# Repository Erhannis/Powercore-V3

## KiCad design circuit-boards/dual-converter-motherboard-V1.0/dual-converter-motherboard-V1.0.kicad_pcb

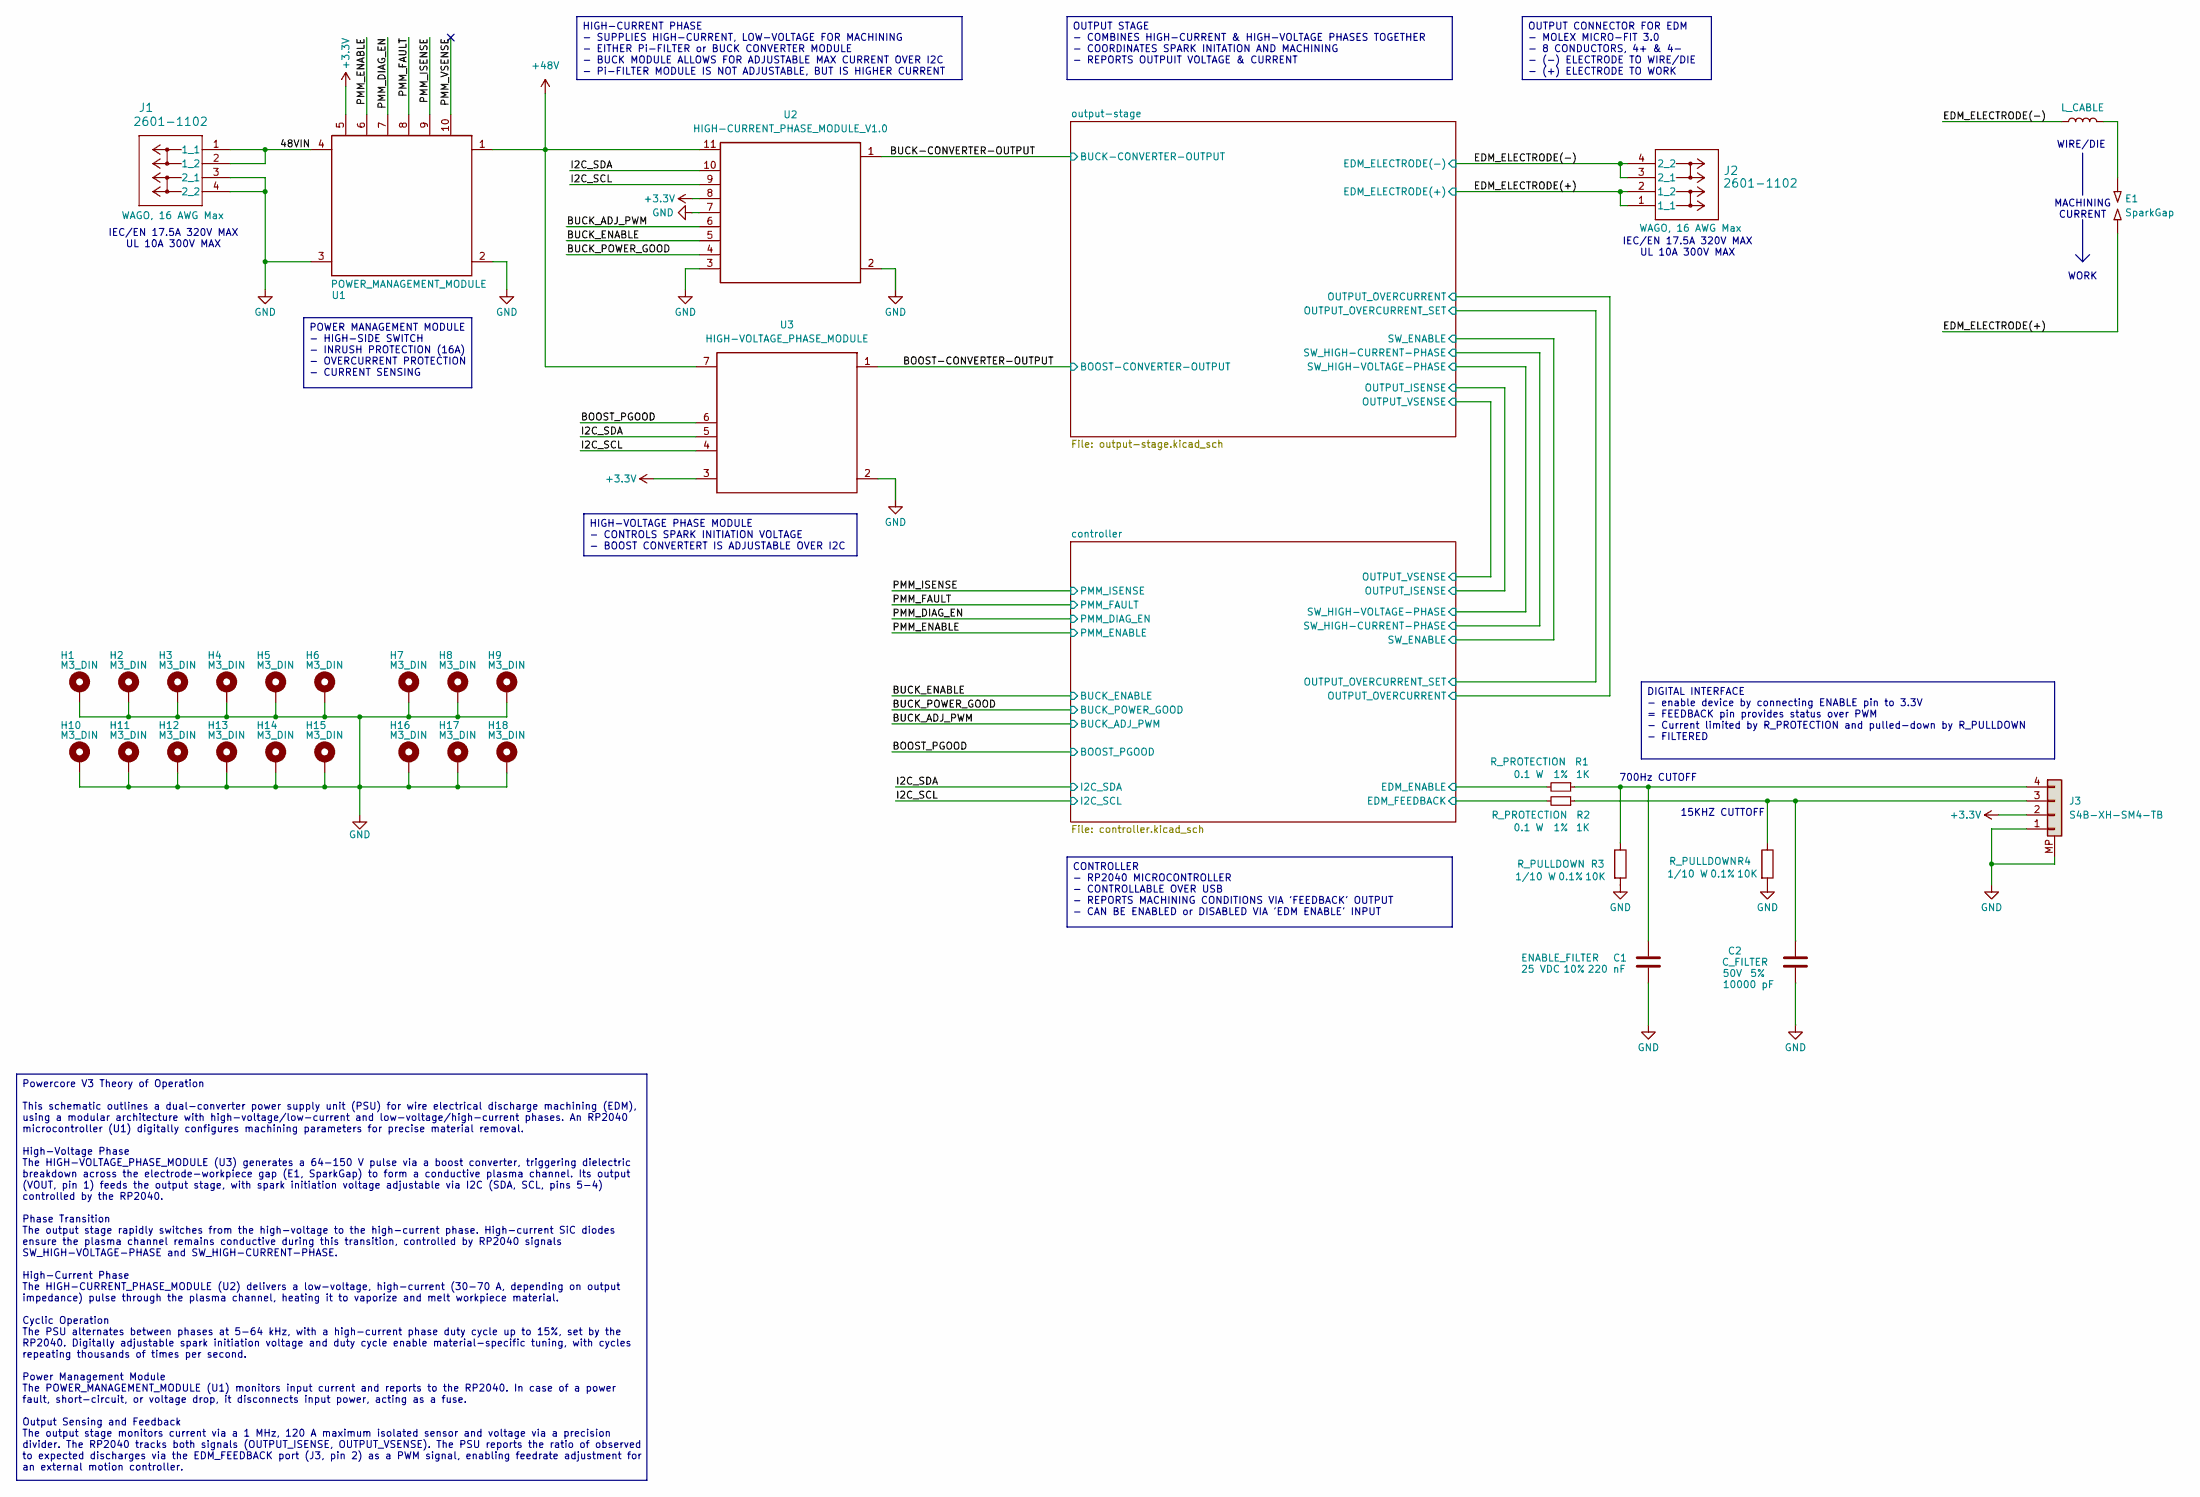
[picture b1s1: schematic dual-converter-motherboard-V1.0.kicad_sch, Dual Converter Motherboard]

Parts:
C1: 220 nF; C_0603_1608Metric; Tolerance 10%; Max Voltage 25 VDC; Manufacturer# AC0603KRX7R9BB224; LCSC Part # C726565
C2: 10000 pF; C_0603_1608Metric; Tolerance 5%; Max Voltage 50V; Manufacturer# CC0603JRX7R9BB103; LCSC Part # C115056
E1: SparkGap; NULL; Manufacturer# NULL; LCSC Part # NULL
H1, H2, H3, H4, H5, H6, H7, H8, H9, H10, H11, H12, H13, H14, H15, H16, H17, H18: M3_DIN; MountingHole_3.2mm_M3_DIN965_Pad_TopBottom; Manufacturer# NULL
J1, J2: 2601-1102; Manufacturer# 2601-1102; LCSC Part # C7509568
J3: S4B-XH-SM4-TB; Manufacturer# S4B-XH-SM4-TB; LCSC Part # C161861
L_CABLE1: L_CABLE
R1, R2: 1K; R_0603_1608Metric; Tolerance 1%; Manufacturer# RC0603FR-071KL; LCSC Part # C22548
R3, R4: 10K; R_0603_1608Metric; Tolerance 0.1%; Manufacturer# RC0603BR-0710KL; LCSC Part # C95204
U1: POWER_MANAGEMENT_MODULE; POWER_MANAGEMENT_MODULE_FOOTPRINT_V1.0
U2: HIGH-CURRENT_PHASE_MODULE_V1.0; HIGH-CURRENT_PHASE_MODULE_FOOTPRINT_V1.0
U3: HIGH-VOLTAGE_PHASE_MODULE; HIGH-VOLTAGE_PHASE_MODULE_FOOTPRINT_V1.0

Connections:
+3.3V: J3.2, U1.5, U2.8 (3.3VIN), U3.3 (GND); also elsewhere on the board
+48V: U1.1 (VOUT), U2.11 (48VIN), U3.7 (48VIN); also elsewhere on the board
/48VIN: J1.1 (1_1), J1.2 (1_2), U1.4 (VIN)
/BOOST-CONVERTER-OUTPUT: U3.1 (VOUT); also elsewhere on the board
/BOOST_PGOOD: U3.6 (PGOOD); also elsewhere on the board
/BUCK-CONVERTER-OUTPUT: U2.1 (VOUT); also elsewhere on the board
/BUCK_ADJ_PWM: U2.6 (PWM_ADJ); also elsewhere on the board
/BUCK_ENABLE: U2.5 (ENABLE); also elsewhere on the board
/BUCK_POWER_GOOD: U2.4 (PGOOD); also elsewhere on the board
/EDM_ELECTRODE(+): E1.1, J2.1 (1_1), J2.2 (1_2); also elsewhere on the board
/EDM_ELECTRODE(-): J2.3 (2_1), J2.4 (2_2), L_CABLE1.1; also elsewhere on the board
/I2C_SCL: U2.9 (SCL), U3.4 (SCL); also elsewhere on the board
/I2C_SDA: U2.10 (SDA), U3.5 (SDA); also elsewhere on the board
/PMM_DIAG_EN: U1.7; also elsewhere on the board
/PMM_ENABLE: U1.6; also elsewhere on the board
/PMM_FAULT: U1.8; also elsewhere on the board
/PMM_ISENSE: U1.9; also elsewhere on the board
/PMM_VSENSE: U1.10
/PMM_VSENSE_1: U1.10
/controller/EDM_ENABLE: R1.2; also elsewhere on the board
/controller/EDM_FEEDBACK: R2.2; also elsewhere on the board
GND: C1.2, C2.2, H1.1, H2.1, H3.1, H4.1, H5.1, H6.1, H7.1, H8.1, H9.1, H10.1, H11.1, H12.1, H13.1, H14.1, H15.1, H16.1, H17.1, H18.1, J1.3 (2_1), J1.4 (2_2), J3.1, J3.MP, R3.2, R4.2, U1.2, U1.3, U2.2 (GND), U2.3 (GND), U2.7 (GND), U3.2 (GND); also elsewhere on the board
unnamed: E1.2, L_CABLE1.2
unnamed: C2.1, J3.3, R2.1, R4.1
unnamed: C1.1, J3.4, R1.1, R3.1

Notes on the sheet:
IEC/EN 17.5A 320V MAX UL 10A 300V MAX
WORK
700Hz CUTOFF
MACHINING CURRENT
WIRE/DIE
15KHZ CUTTOFF
CONTROLLER - RP2040 MICROCONTROLLER - CONTROLLABLE OVER USB - REPORTS MACHINING CONDITIONS VIA 'FEEDBACK' OUTPUT - CAN BE ENABLED or DISABLED VIA 'EDM ENABLE' INPUT
HIGH-VOLTAGE PHASE MODULE - CONTROLS SPARK INITIATION VOLTAGE - BOOST CONVERTERT IS ADJUSTABLE OVER I2C
OUTPUT CONNECTOR FOR EDM - MOLEX MICRO-FIT 3.0 - 8 CONDUCTORS, 4+ & 4- - (-) ELECTRODE TO WIRE/DIE - (+) ELECTRODE TO WORK
HIGH-CURRENT PHASE - SUPPLIES HIGH-CURRENT, LOW-VOLTAGE FOR MACHINING - EITHER Pi-FILTER or BUCK CONVERTER MODULE - BUCK MODULE ALLOWS FOR ADJUSTABLE MAX CURRENT OVER I2C - Pi-FILTER MODULE IS NOT ADJUSTABLE, BUT IS HIGHER CURRENT
Powercore V3 Theory of Operation This schematic outlines a dual-converter power supply unit (PSU) for wire electrical discharge machining (EDM), using a modular architecture with high-voltage/low-current and low-voltage/high-current phases. An RP2040 microcontroller (U1) digitally configures machin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
OUTPUT STAGE - COMBINES HIGH-CURRENT & HIGH-VOLTAGE PHASES TOGETHER - COORDINATES SPARK INITATION AND MACHINING - REPORTS OUTPUIT VOLTAGE & CURRENT
POWER MANAGEMENT MODULE - HIGH-SIDE SWITCH - INRUSH PROTECTION (16A) - OVERCURRENT PROTECTION - CURRENT SENSING
DIGITAL INTERFACE - enable device by connecting ENABLE pin to 3.3V = FEEDBACK pin provides status over PWM - Current limited by R_PROTECTION and pulled-down by R_PULLDOWN - FILTERED

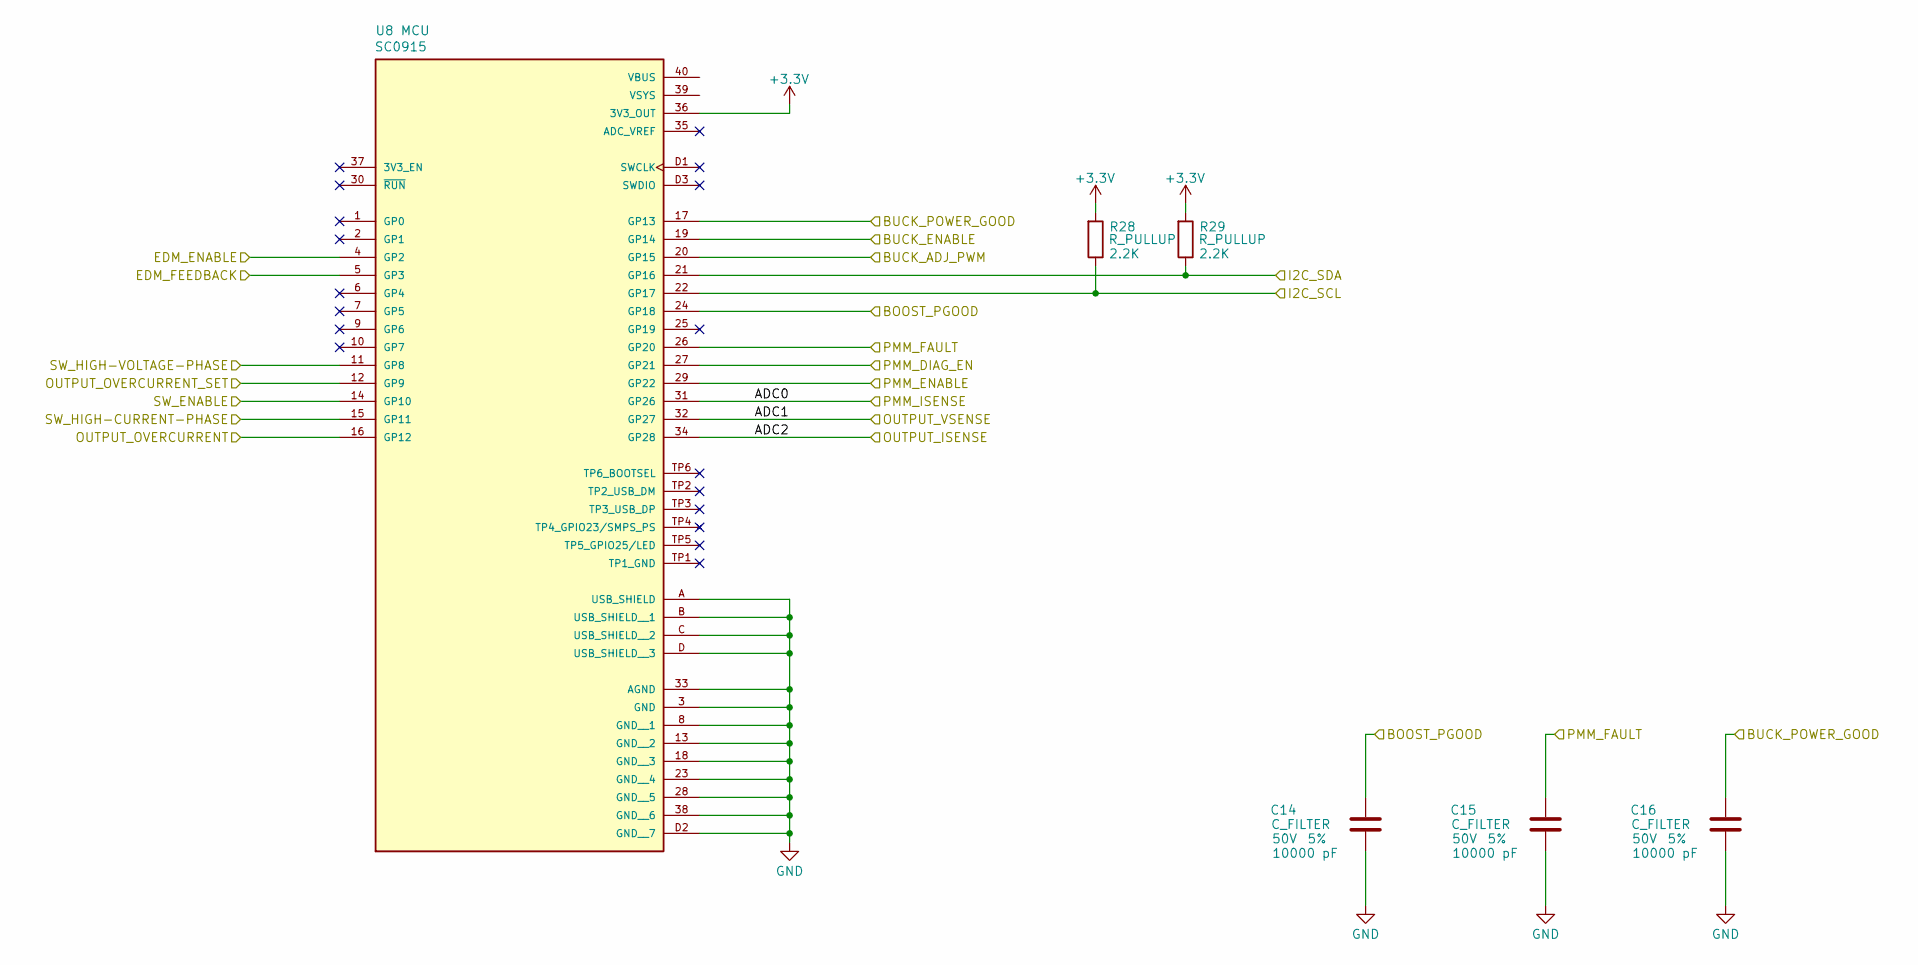
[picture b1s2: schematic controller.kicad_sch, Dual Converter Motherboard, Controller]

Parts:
C14, C15, C16: 10000 pF; C_0603_1608Metric; Tolerance 5%; Max Voltage 50V; Manufacturer# CC0603JRX7R9BB103; LCSC Part # C115056
R28, R29: 2.2K; R_0603_1608Metric; Tolerance 1%; Manufacturer# RC0603FR-132K2L; LCSC Part # C3032396
U8: SC0915; Manufacturer# SC0915; LCSC Part # C7203002

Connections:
+3.3V: R28.2, R29.2, U8.36 (3V3_OUT); also elsewhere on the board
/BOOST_PGOOD: C14.1, U8.24 (GP18); also elsewhere on the board
/BUCK_ADJ_PWM: U8.20 (GP15); also elsewhere on the board
/BUCK_ENABLE: U8.19 (GP14); also elsewhere on the board
/BUCK_POWER_GOOD: C16.1, U8.17 (GP13); also elsewhere on the board
/I2C_SCL: R28.1, U8.22 (GP17); also elsewhere on the board
/I2C_SDA: R29.1, U8.21 (GP16); also elsewhere on the board
/PMM_DIAG_EN: U8.27 (GP21); also elsewhere on the board
/PMM_ENABLE: U8.29 (GP22); also elsewhere on the board
/PMM_FAULT: C15.1, U8.26 (GP20); also elsewhere on the board
/PMM_ISENSE: U8.31 (GP26); also elsewhere on the board
/controller/ADC1: U8.32 (GP27); also elsewhere on the board
/controller/ADC2: U8.34 (GP28); also elsewhere on the board
/controller/EDM_ENABLE: U8.4 (GP2); also elsewhere on the board
/controller/EDM_FEEDBACK: U8.5 (GP3); also elsewhere on the board
/controller/OUTPUT_OVERCURRENT: U8.16 (GP12); also elsewhere on the board
/controller/OUTPUT_OVERCURRENT_SET: U8.12 (GP9); also elsewhere on the board
/controller/SW_ENABLE: U8.14 (GP10); also elsewhere on the board
/controller/SW_HIGH-CURRENT-PHASE: U8.15 (GP11); also elsewhere on the board
/controller/SW_HIGH-VOLTAGE-PHASE: U8.11 (GP8); also elsewhere on the board
GND: C14.2, C15.2, C16.2, U8.3 (GND), U8.8 (GND__1), U8.13 (GND__2), U8.18 (GND__3), U8.23 (GND__4), U8.28 (GND__5), U8.33 (AGND), U8.38 (GND__6), U8.A (USB_SHIELD), U8.B (USB_SHIELD__1), U8.C (USB_SHIELD__2), U8.D (USB_SHIELD__3), U8.D2 (GND__7); also elsewhere on the board

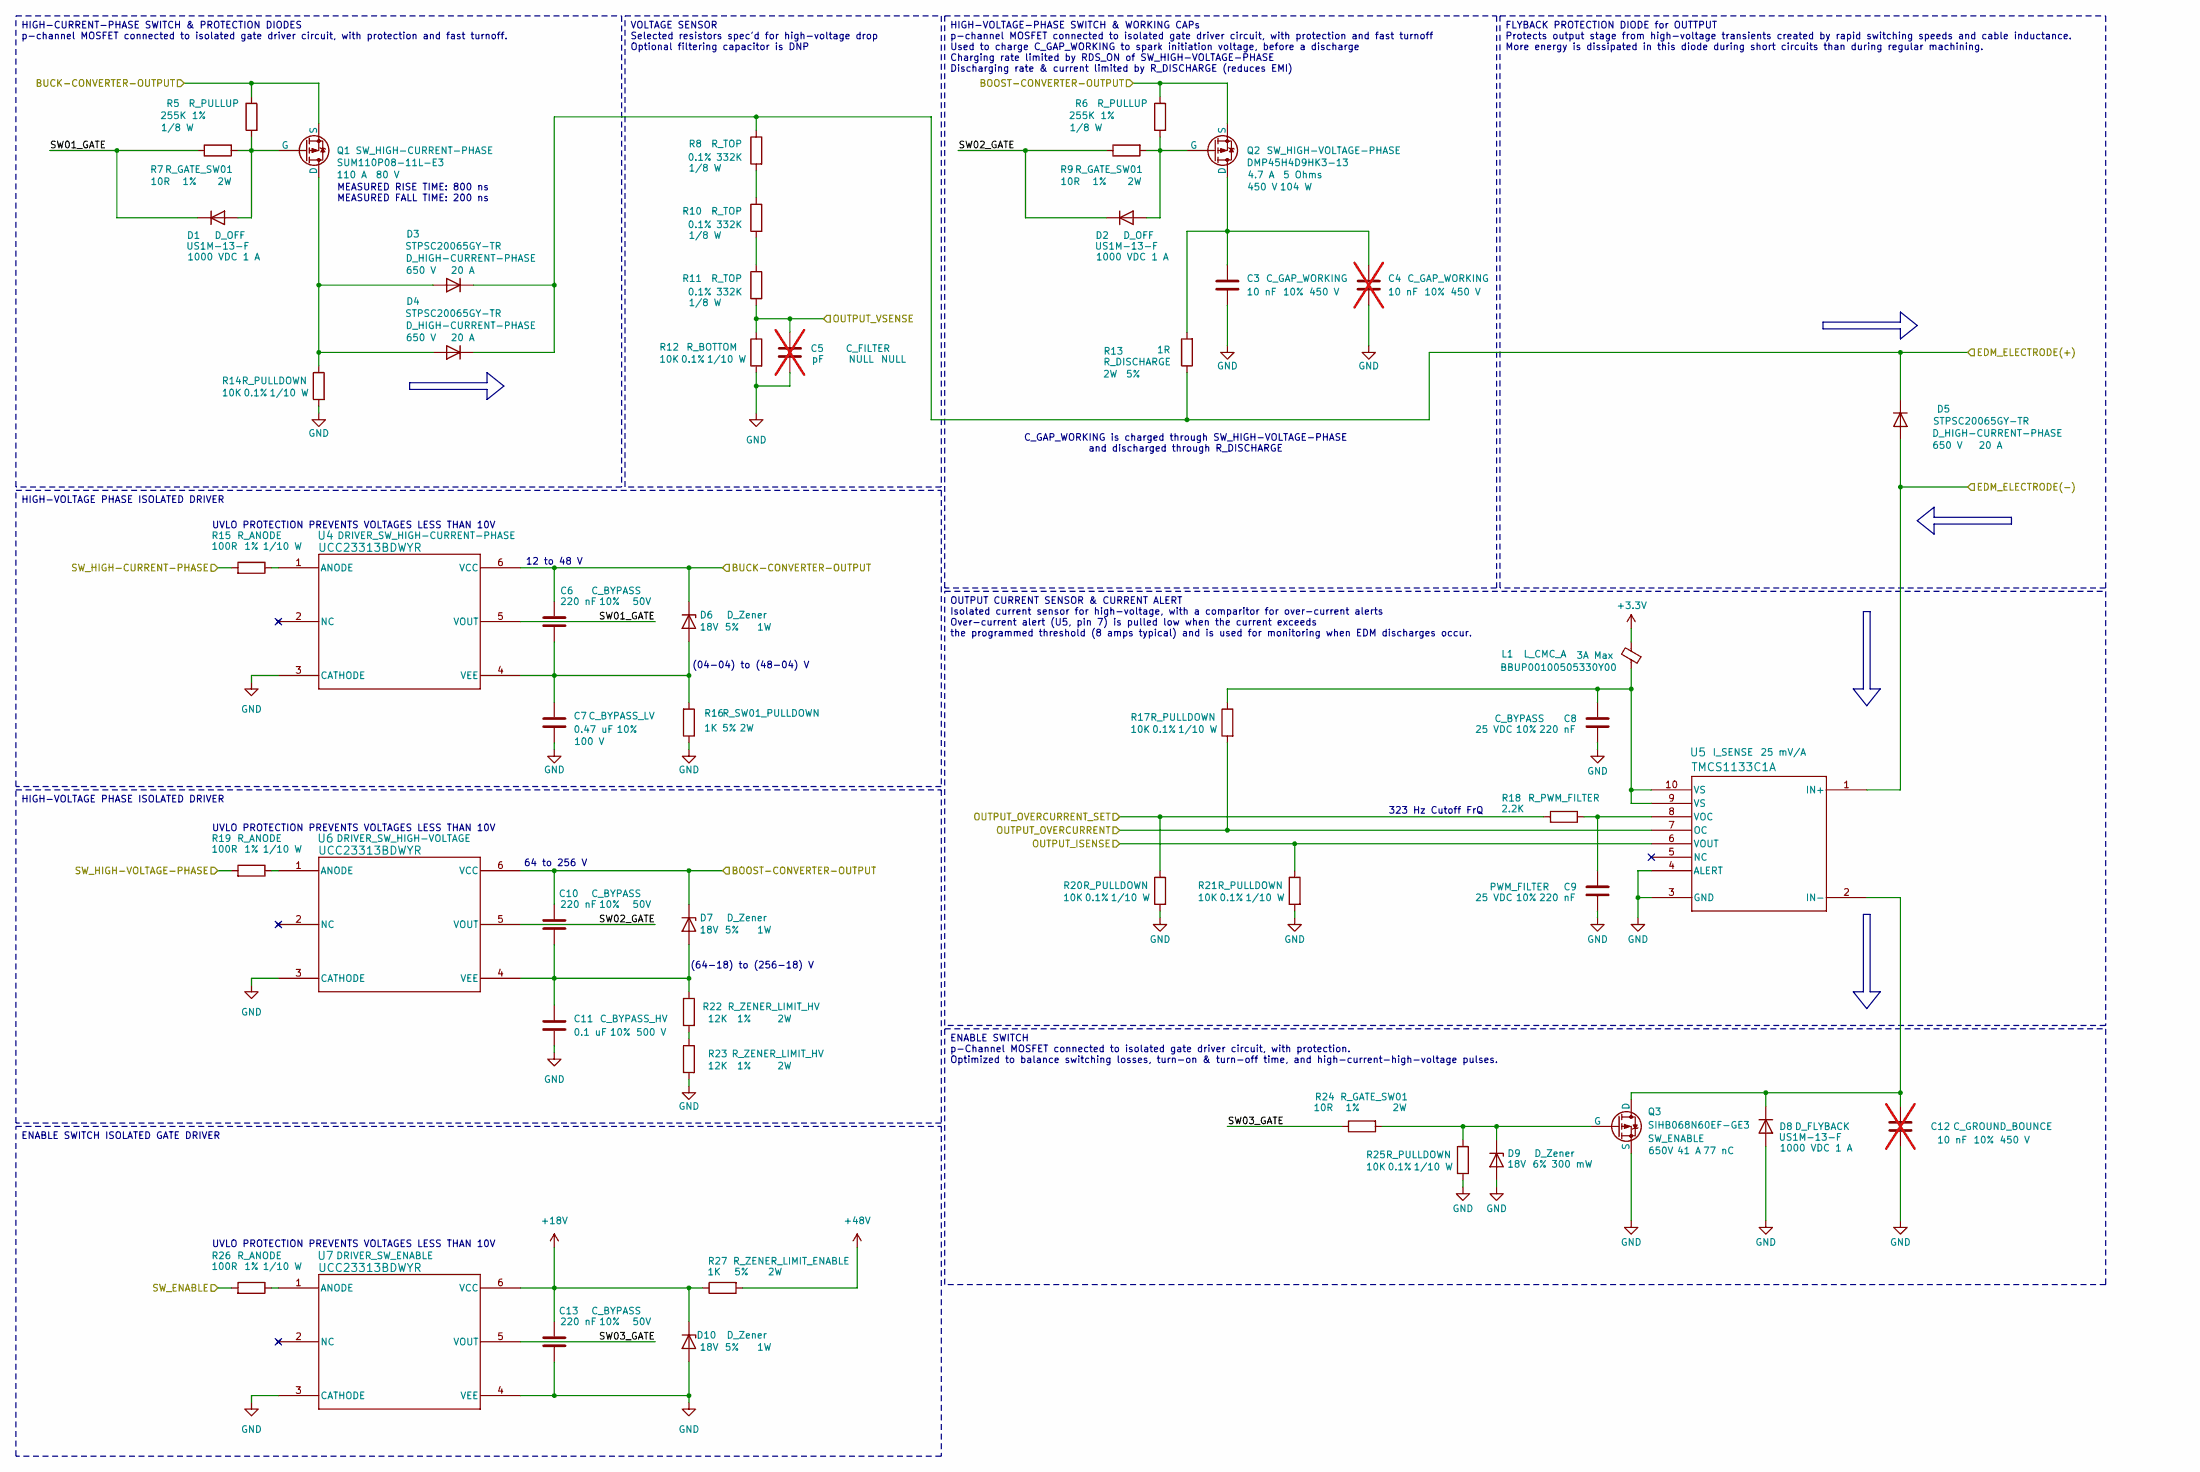
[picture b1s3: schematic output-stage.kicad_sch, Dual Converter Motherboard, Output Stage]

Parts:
C3: 10 nF; C_0805_2012Metric; Tolerance 10%; Max Voltage 450 V; Manufacturer# C2012X7T2W103K085AA; LCSC Part # C342860
C4, C12: 10 nF; C_0805_2012Metric; Tolerance 10%; Max Voltage 450 V; Manufacturer# C2012X7T2W103K085AA; LCSC Part # C342860; not fitted
C5: pF; C_0603_1608Metric; Tolerance NULL; Max Voltage NULL; Manufacturer# NULL; LCSC Part # NULL; not fitted
C6, C10, C13: 220 nF; C_0603_1608Metric; Tolerance 10%; Max Voltage 50V; Manufacturer# AC0603KRX7R9BB224; LCSC Part # C726565
C7: 0.47 uF; C_0805_2012Metric; Tolerance 10%; Max Voltage 100 V; Manufacturer# CC0805KKX7R0BB474; LCSC Part # C596323
C8, C9: 220 nF; C_0603_1608Metric; Tolerance 10%; Max Voltage 25 VDC; Manufacturer# AC0603KRX7R9BB224; LCSC Part # C726565
C11: 0.1 uF; C_1210_3225Metric; Tolerance 10%; Max Voltage 500 V; Manufacturer# C1210C104KCRACTU; LCSC Part # C141218
D1, D2, D8: US1M-13-F; D_SMA; Tolerance NULL; Manufacturer# US1M-13-F; LCSC Part # C99333
D3, D4, D5: STPSC20065GY-TR; Tolerance NULL; Manufacturer# STPSC20065GY-TR; LCSC Part # C2965441
D6, D7, D10: D_Zener; D_SMA; Zener Voltage 18V; Tolerance 5%; Manufacturer# SMAZ18-13-F; LCSC Part # C110525
D9: D_Zener; D_SOD-323; Zener Voltage 18V; Tolerance 6%; Manufacturer# MM3Z18VT1G; LCSC Part # C82043
L1: BBUP00100505330Y00; L_0402_1005Metric; Manufacturer# BLM15AX100SN1D; LCSC Part # C668299
Q1: SUM110P08-11L-E3; Max Voltage 80 V; Manufacturer# SUM110P08-11L-E3; LCSC Part # C2838509
Q2: DMP45H4D9HK3-13; Max Voltage 450 V; Manufacturer# DMP45H4D9HK3-13; LCSC Part # C3281371
Q3: SIHB068N60EF-GE3; TO-263-2; Max Voltage 650V; Manufacturer# SIHB068N60EF-GE3; LCSC Part # C3009875
R5, R6: 255K; R_0603_1608Metric; Tolerance 1%; Manufacturer# RC0603FR-07255KL; LCSC Part # C295887
R7, R9, R24: 10R; R_2512_6332Metric; Tolerance 1%; Manufacturer# SR2512JK-7W10RL; LCSC Part # C3013385
R8, R10, R11: 332K; R_0805_2012Metric; Tolerance 0.1%; Manufacturer# RT0805BRD07332KL; LCSC Part # C865409
R12, R14, R17, R20, R21, R25: 10K; R_0603_1608Metric; Tolerance 0.1%; Manufacturer# RC0603BR-0710KL; LCSC Part # C95204
R13: 1R; R_2512_6332Metric; Tolerance 5%; Manufacturer# CRM2512-JW-1R0ELF; LCSC Part # C840599
R15, R19, R26: 100R; R_0603_1608Metric; Tolerance 1%; Manufacturer# RC0603FR-10100RL; LCSC Part # C22775
R16, R27: 1K; R_2512_6332Metric; Tolerance 5%; Manufacturer# RES 1K OHM 5% 2W 2512; LCSC Part # C7038808
R18: 2.2K; R_0603_1608Metric; Tolerance 1%; Manufacturer# RC0603FR-132K2L; LCSC Part # C3032396
R22, R23: 12K; R_2512_6332Metric; Tolerance 1%; Manufacturer# CRGP2512F12K; LCSC Part # C2082818
U4, U6, U7: UCC23313BDWYR; Tolerance NULL; Manufacturer# UCC23313BDWYR; LCSC Part # C2868027
U5: TMCS1133C1A; TMCS1133C3AQDVGR; Tolerance 1%; Manufacturer# TMCS1133C1AQDVGR; LCSC Part # C32266987

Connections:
+3.3V: L1.2; also elsewhere on the board
+18V: C13.1, D10.1 (K), R27.1, U7.6 (VCC)
+48V: R27.2; also elsewhere on the board
/BOOST-CONVERTER-OUTPUT: C10.1, D7.1 (K), Q2.3 (S), R6.1, U6.6 (VCC); also elsewhere on the board
/BUCK-CONVERTER-OUTPUT: C6.1, D6.1 (K), Q1.3 (S), R5.1, U4.6 (VCC); also elsewhere on the board
/EDM_ELECTRODE(+): D3.1 (K), D4.1 (K), D5.1 (K), R8.1, R13.1; also elsewhere on the board
/EDM_ELECTRODE(-): D5.2 (A), U5.1 (IN+); also elsewhere on the board
/controller/ADC1: C5.1, R11.2, R12.1; also elsewhere on the board
/controller/ADC2: R21.1, U5.6 (VOUT); also elsewhere on the board
/controller/OUTPUT_OVERCURRENT: R17.2, U5.7 (OC); also elsewhere on the board
/controller/OUTPUT_OVERCURRENT_SET: R18.1, R20.1; also elsewhere on the board
/controller/SW_ENABLE: R26.2; also elsewhere on the board
/controller/SW_HIGH-CURRENT-PHASE: R15.2; also elsewhere on the board
/controller/SW_HIGH-VOLTAGE-PHASE: R19.2; also elsewhere on the board
/output-stage/SW01_GATE: D1.1 (K), R7.1, U4.5 (VOUT)
/output-stage/SW02_GATE: D2.1 (K), R9.1, U6.5 (VOUT)
/output-stage/SW03_GATE: R24.1, U7.5 (VOUT)
GND: C3.2, C4.2, C5.2, C7.2, C8.2, C9.2, C11.2, C12.2, C13.2, D8.2 (A), D9.2 (A), D10.2 (A), Q3.3 (S), R12.2, R14.2, R16.1, R20.2, R21.2, R23.2, R25.2, U4.3 (CATHODE), U5.3 (GND), U5.4 (ALERT), U6.3 (CATHODE), U7.3 (CATHODE), U7.4 (VEE); also elsewhere on the board
unnamed: C8.1, L1.1, R17.1, U5.9 (VS), U5.10 (VS)
unnamed: D1.2 (A), Q1.2 (G), R5.2, R7.2
unnamed: D2.2 (A), Q2.2 (G), R6.2, R9.2
unnamed: D3.2 (A), D4.2 (A), Q1.1 (D), R14.1
unnamed: C6.2, C7.1, D6.2 (A), R16.2, U4.4 (VEE)
unnamed: C10.2, C11.1, D7.2 (A), R22.1, U6.4 (VEE)
unnamed: C12.1, D8.1 (K), Q3.2 (D), U5.2 (IN-)
unnamed: D9.1 (K), Q3.1 (G), R24.2, R25.1
unnamed: C3.1, C4.1, Q2.1 (D), R13.2
unnamed: R8.2, R10.1
unnamed: R10.2, R11.1
unnamed: R22.2, R23.1
unnamed: R15.1, U4.1 (ANODE)
unnamed: C9.1, R18.2, U5.8 (VOC)
unnamed: R19.1, U6.1 (ANODE)
unnamed: R26.1, U7.1 (ANODE)

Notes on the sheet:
UVLO PROTECTION PREVENTS VOLTAGES LESS THAN 10V
C_GAP_WORKING is charged through SW_HIGH-VOLTAGE-PHASE and discharged through R_DISCHARGE
323 Hz Cutoff FrQ
(04-04) to (48-04) V
12 to 48 V
(64-18) to (256-18) V
64 to 256 V
MEASURED RISE TIME: 800 ns MEASURED FALL TIME: 200 ns
FLYBACK PROTECTION DIODE for OUTTPUT Protects output stage from high-voltage transients created by rapid switching speeds and cable inductance. More energy is dissipated in this diode during short circuits than during regular machining.
HIGH-VOLTAGE PHASE ISOLATED DRIVER
ENABLE SWITCH ISOLATED GATE DRIVER
ENABLE SWITCH p-Channel MOSFET connected to isolated gate driver circuit, with protection. Optimized to balance switching losses, turn-on & turn-off time, and high-current-high-voltage pulses.
HIGH-VOLTAGE-PHASE SWITCH & WORKING CAPs p-channel MOSFET connected to isolated gate driver circuit, with protection and fast turnoff Used to charge C_GAP_WORKING to spark initiation voltage, before a discharge Charging rate limited by RDS_ON of SW_HIGH-VOLTAGE-PHASE Discharging rate & current limi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
OUTPUT CURRENT SENSOR & CURRENT ALERT Isolated current sensor for high-voltage, with a comparitor for over-current alerts Over-current alert (U5, pin 7) is pulled low when the current exceeds the programmed threshold (8 amps typical) and is used for monitoring when EDM discharges occur.
VOLTAGE SENSOR Selected resistors spec'd for high-voltage drop Optional filtering capacitor is DNP
HIGH-CURRENT-PHASE SWITCH & PROTECTION DIODES p-channel MOSFET connected to isolated gate driver circuit, with protection and fast turnoff.

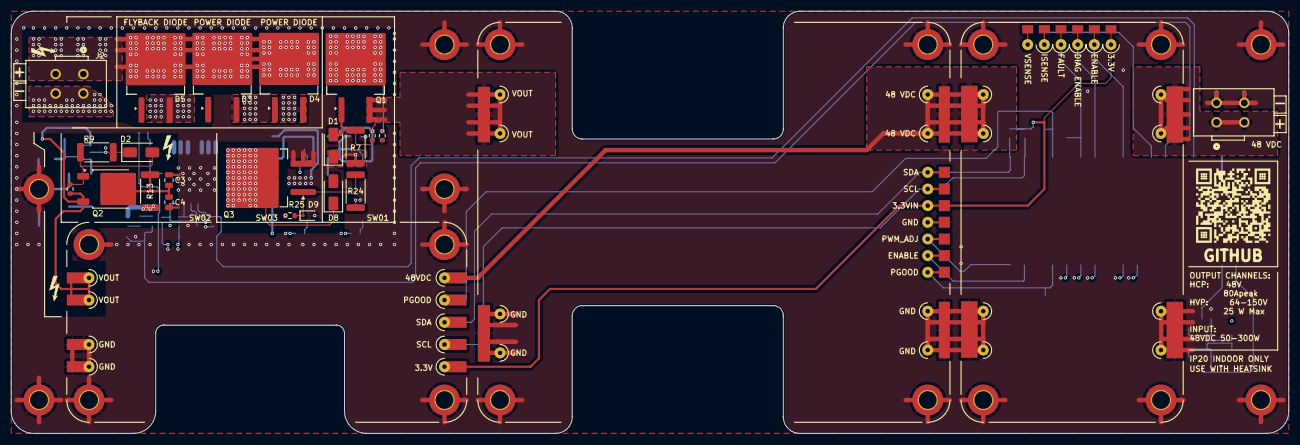
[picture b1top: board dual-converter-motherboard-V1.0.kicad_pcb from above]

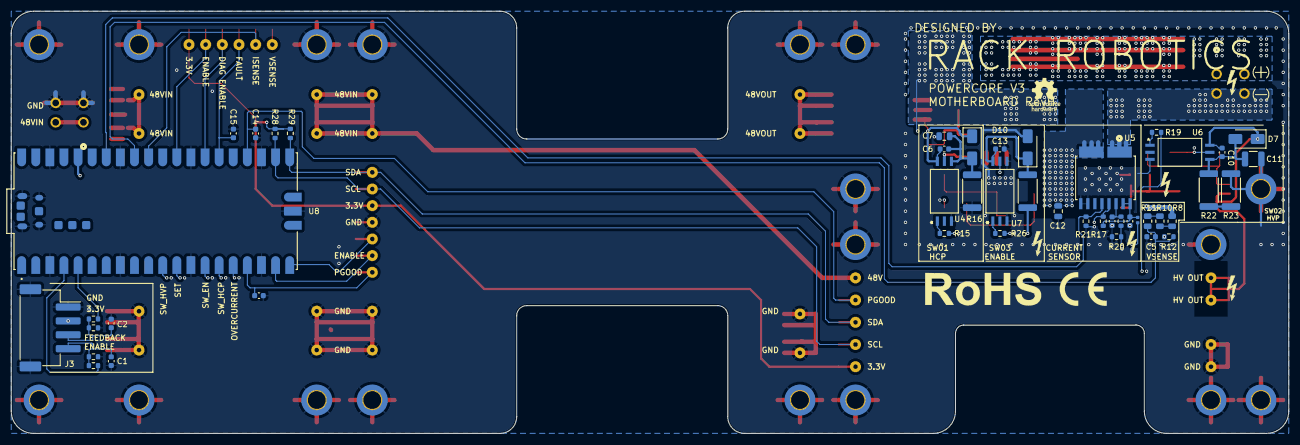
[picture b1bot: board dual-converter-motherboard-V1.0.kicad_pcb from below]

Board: 6 copper layers, 230.0 x 76.0 mm, 118 parts (45 on the bottom side), 49 nets.

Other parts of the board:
POGO1, POGO2, POGO3, POGO4, POGO5, POGO6, POGO7, POGO8, POGO9, POGO10, POGO11, POGO12, POGO13, POGO14, POGO15, POGO16, POGO17, POGO18, POGO19, POGO20, POGO21, POGO22, POGO23, POGO24, POGO25, POGO26, POGO27, POGO28, POGO29, POGO30: 0906-8-15-20-76-14-11-0

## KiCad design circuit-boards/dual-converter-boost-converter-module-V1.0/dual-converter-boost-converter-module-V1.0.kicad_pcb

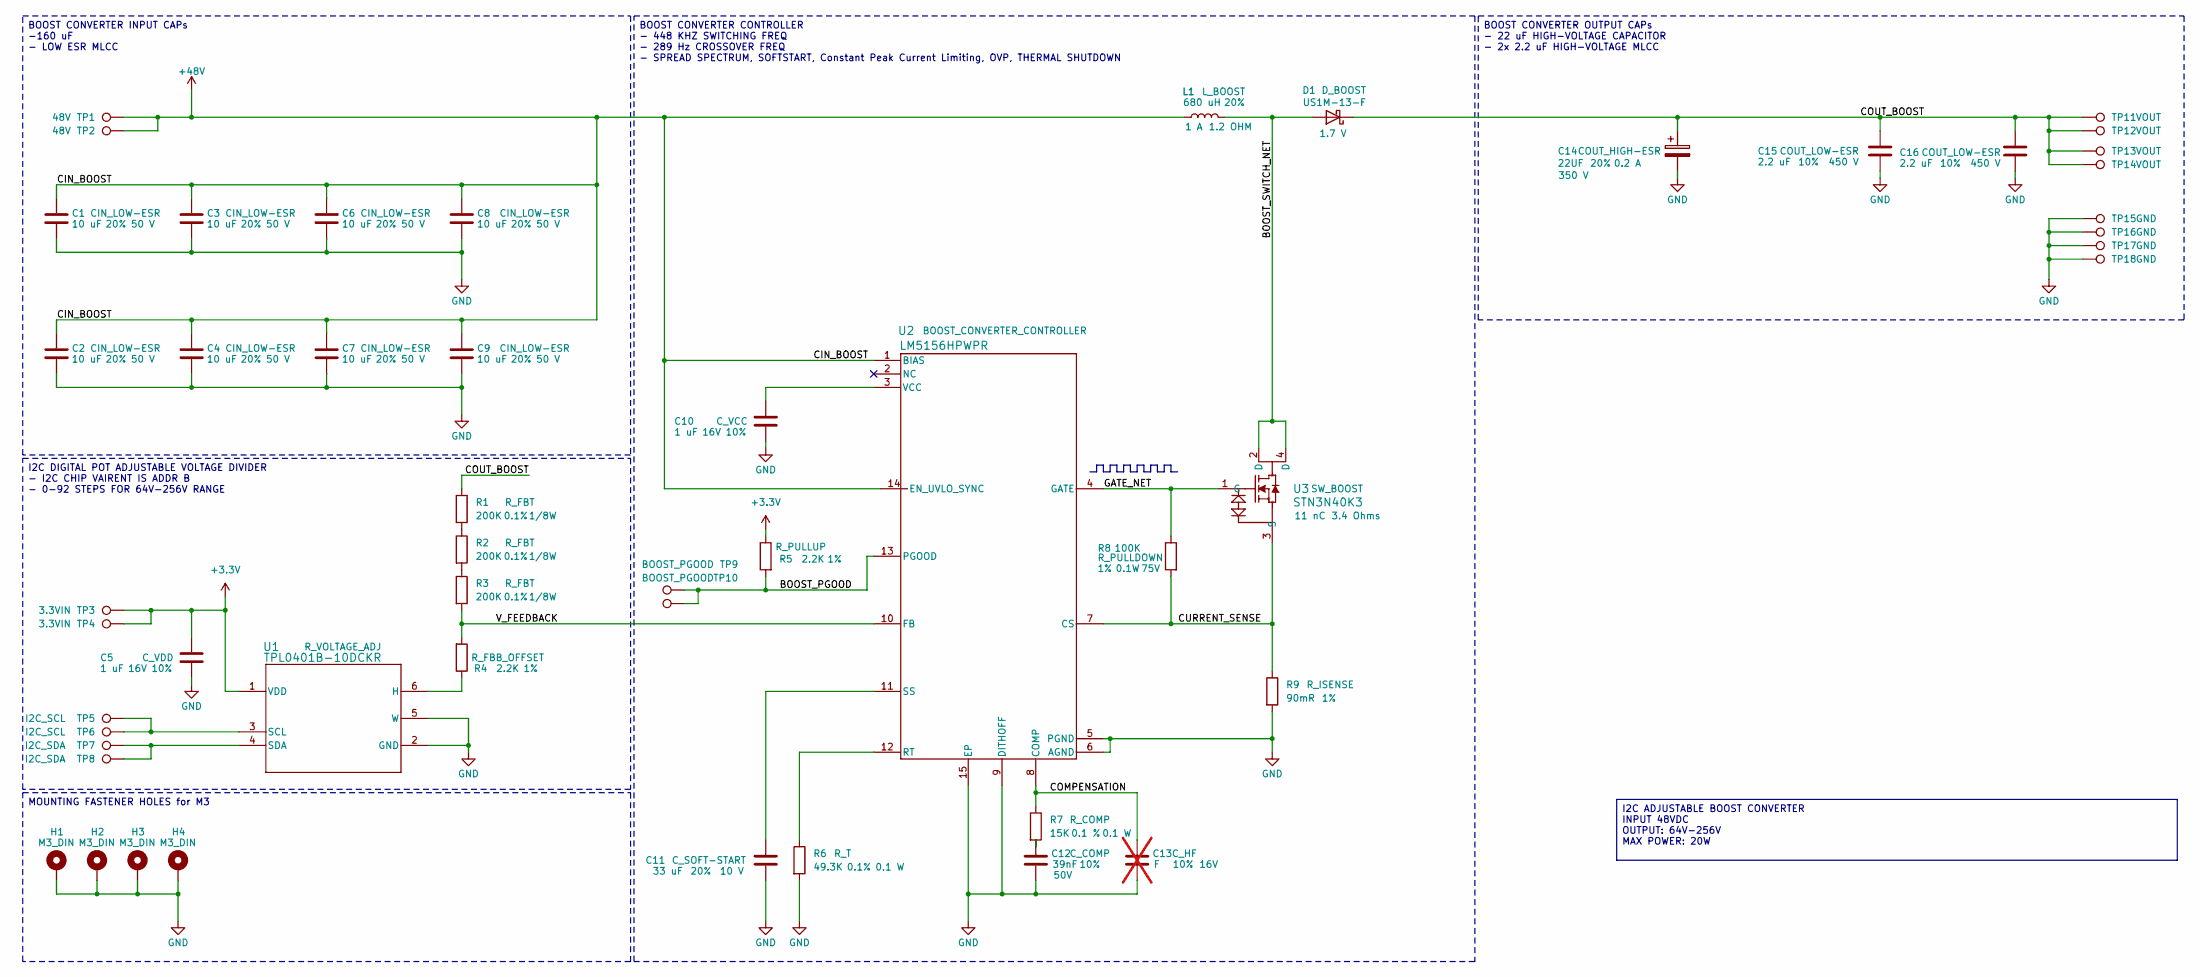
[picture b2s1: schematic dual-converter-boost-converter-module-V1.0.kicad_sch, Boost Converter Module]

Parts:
C1, C2, C3, C4, C6, C7, C8, C9: 10 uF; C_1206_3216Metric; Tolerance 20%; Max Voltage 50 V; Manufacturer# CL31A106MBHNNNE; LCSC Part # C96600
C5, C10: 1 uF; C_0603_1608Metric; Tolerance 10%; Max Voltage 16V; Manufacturer# CC0603KRX5R7BB105; LCSC Part # C106215
C11: 33 uF; C_0805_2012Metric; Tolerance 20%; Max Voltage 10 V; Manufacturer# C2012X5R1A336MTJ00E; LCSC Part # C342635
C12: 39nF; C_0603_1608Metric; Tolerance 10%; Max Voltage 50V; Manufacturer# CC0603KRX7R9BB393; LCSC Part # C107091
C13: F; C_0603_1608Metric; Tolerance 10%; Max Voltage 16V; Manufacturer# NULL; LCSC Part # NULL; not fitted
C14: 22UF; 226TTA350M; Tolerance 20%; Max Voltage 350 V; Manufacturer# 226TTA350M; LCSC Part # C6077372
C15, C16: 2.2 uF; C_2220_5750Metric; Tolerance 10%; Max Voltage 450 V; Manufacturer# TDK Corporation; LCSC Part # C445674
D1: US1M-13-F; D_SMA; Forward Voltage 1.7 V; Manufacturer# US1M-13-F; LCSC Part # C99333
H1, H2, H3, H4: M3_DIN; MountingHole_3.2mm_M3_DIN965_Pad_TopBottom; Manufacturer# NULL
L1: 680 uH; SRR1210-681M; Tolerance 20%; Manufacturer# SRR1210-681M; LCSC Part # C1329591
R1, R2, R3: 200K; R_0805_2012Metric; Tolerance 0.1%; Manufacturer# RT0805BRD07200KL; LCSC Part # C728645
R4, R5: 2.2K; R_0603_1608Metric; Tolerance 1%; Manufacturer# 13-RC0603FR-132K2LCT-ND; LCSC Part # C3032396
R6: 49.3K; R_0603_1608Metric; Tolerance 0.1%; Manufacturer# AT0603BRD0749K3L; LCSC Part # C5455477
R7: 15K; R_0603_1608Metric; Tolerance 0.1 %; Manufacturer# AT0603BRD0715KL; LCSC Part # C855633
R8: 100K; R_0603_1608Metric; Tolerance 1%; Max Voltage 75V; Manufacturer# CRCW0603100KFKEA; LCSC Part # C844916
R9: 90mR; R_1206_3216Metric; Tolerance 1%; Manufacturer# RL1206FR-070R09L; LCSC Part # C5121023
TP1, TP2: 48V; TestPoint_TestPoint_Pad_2.0x2.0mm_No_Silkscreen; Manufacturer# NULL
TP3, TP4: 3.3VIN; TestPoint_TestPoint_Pad_2.0x2.0mm_No_Silkscreen; Manufacturer# NULL
TP5, TP6: I2C_SCL; TestPoint_TestPoint_Pad_2.0x2.0mm_No_Silkscreen; Manufacturer# NULL
TP7, TP8: I2C_SDA; TestPoint_TestPoint_Pad_2.0x2.0mm_No_Silkscreen; Manufacturer# NULL
TP9, TP10: BOOST_PGOOD; TestPoint_TestPoint_Pad_2.0x2.0mm_No_Silkscreen; Manufacturer# NULL
TP11, TP12, TP13, TP14: VOUT; TestPoint_TestPoint_Pad_2.0x2.0mm_No_Silkscreen; Manufacturer# NULL
TP15, TP16, TP17, TP18: GND; TestPoint_TestPoint_Pad_2.0x2.0mm_No_Silkscreen; Manufacturer# NULL
U1: TPL0401B-10DCKR; Manufacturer# TPL0401B-10DCKR; LCSC Part # C2666599
U2: LM5156HPWPR; lm5156h; Manufacturer# LM5156HPWPR; LCSC Part # C2867852
U3: STN3N40K3; Manufacturer# STN3N40K3; LCSC Part # C128261

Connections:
+3.3V: C5.1, R5.1, TP3.1, TP4.1, U1.1 (VDD)
+48V: C1.1, C2.1, C3.1, C4.1, C6.1, C7.1, C8.1, C9.1, L1.1, TP1.1, TP2.1, U2.1 (BIAS), U2.14 (EN_UVLO_SYNC)
/BOOST_PGOOD: R5.2, TP9.1, TP10.1, U2.13 (PGOOD)
/BOOST_SWITCH_NET: D1.2 (A), L1.2, U3.2 (D), U3.4 (D)
/COMPENSATION: C13.1, R7.1, U2.8 (COMP)
/COUT_BOOST: C14.1, C15.1, C16.1, D1.1 (K), R1.1, TP11.1, TP12.1, TP13.1, TP14.1
/CURRENT_SENSE: R8.2, R9.1, U2.7 (CS), U3.3 (S)
/GATE_NET: R8.1, U2.4 (GATE), U3.1 (G)
/V_FEEDBACK: R3.2, R4.2, U2.10 (FB)
GND: C1.2, C2.2, C3.2, C4.2, C5.2, C6.2, C7.2, C8.2, C9.2, C10.2, C11.2, C12.2, C13.2, C14.2, C15.2, C16.2, H1.1, H2.1, H3.1, H4.1, R6.2, R9.2, TP15.1, TP16.1, TP17.1, TP18.1, U1.2 (GND), U1.5 (W), U2.5 (PGND), U2.6 (AGND), U2.9 (DITHOFF), U2.15 (EP)
unnamed: C12.1, R7.2
unnamed: R1.2, R2.1
unnamed: R2.2, R3.1
unnamed: R4.1, U1.6 (H)
unnamed: TP5.1, TP6.1, U1.3 (SCL)
unnamed: TP7.1, TP8.1, U1.4 (SDA)
unnamed: R6.1, U2.12 (RT)
unnamed: C11.1, U2.11 (SS)
unnamed: C10.1, U2.3 (VCC)

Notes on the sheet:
BOOST CONVERTER CONTROLLER - 448 KHZ SWITCHING FREQ - 289 Hz CROSSOVER FREQ - SPREAD SPECTRUM, SOFTSTART, Constant Peak Current Limiting, OVP, THERMAL SHUTDOWN
BOOST CONVERTER INPUT CAPs -160 uF - LOW ESR MLCC
I2C DIGITAL POT ADJUSTABLE VOLTAGE DIVIDER - I2C CHIP VAIRENT IS ADDR B - 0-92 STEPS FOR 64V-256V RANGE
MOUNTING FASTENER HOLES for M3
BOOST CONVERTER OUTPUT CAPs - 22 uF HIGH-VOLTAGE CAPACITOR - 2x 2.2 uF HIGH-VOLTAGE MLCC
I2C ADJUSTABLE BOOST CONVERTER INPUT 48VDC OUTPUT: 64V-256V MAX POWER: 20W

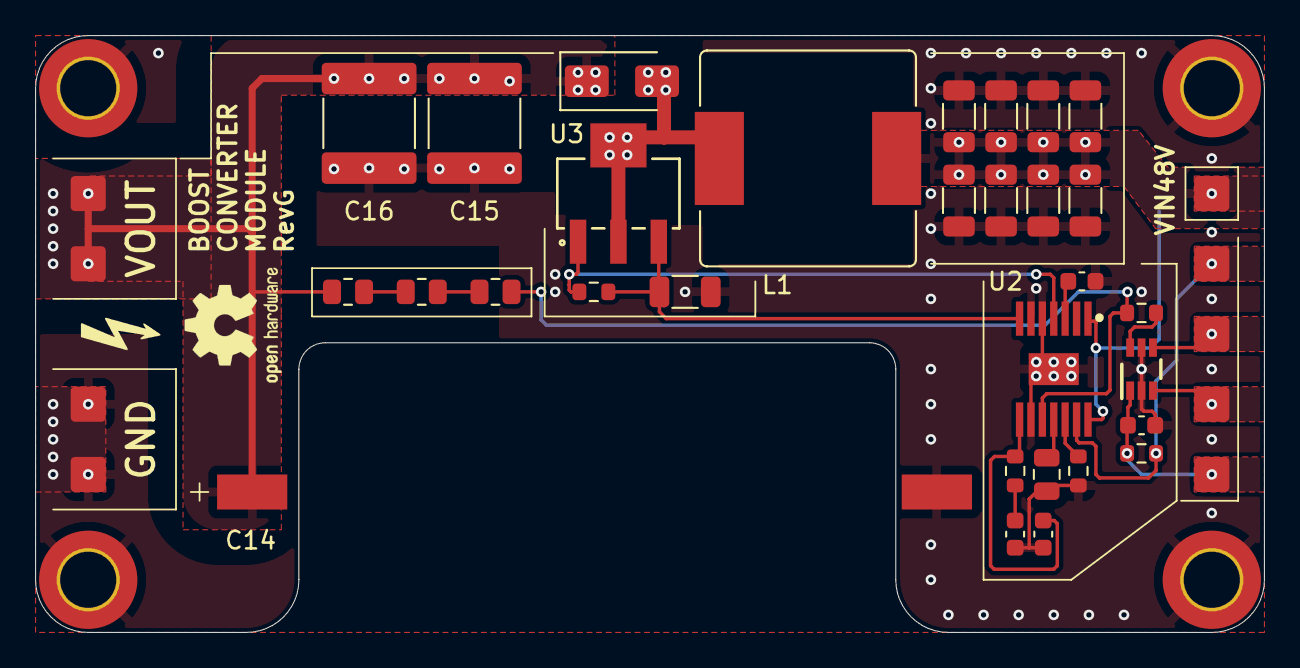
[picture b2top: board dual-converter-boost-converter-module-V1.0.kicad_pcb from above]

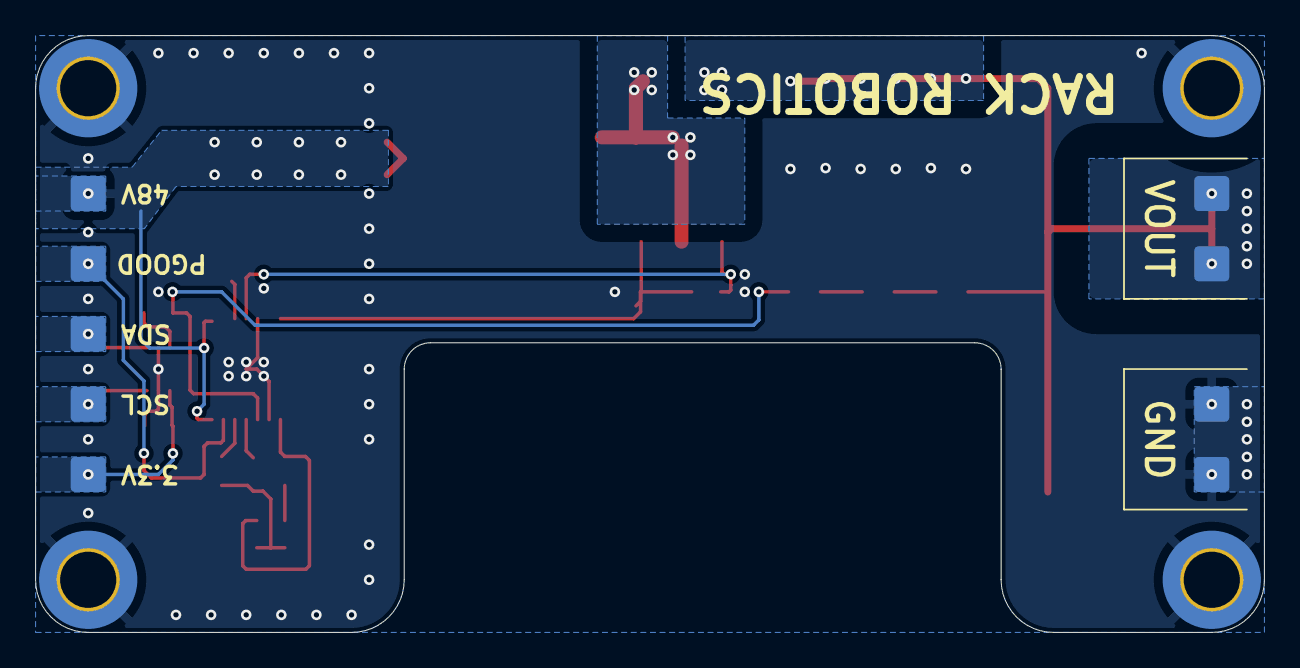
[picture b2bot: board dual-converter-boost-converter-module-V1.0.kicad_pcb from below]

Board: 4 copper layers, 70.0 x 34.0 mm, 52 parts (9 on the bottom side), 19 nets.
